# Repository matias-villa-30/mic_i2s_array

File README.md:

# mic_array: 3-microphone sound direction finder (Raspberry Pi Pico 2)

Three I2S MEMS microphones sampled in lockstep by a Raspberry Pi Pico 2, bare metal, no RTOS. The firmware measures **how many samples later each microphone hears a sound** (TDOA, time difference of arrival) and turns those delays into an **azimuth angle** toward the source.

> **Purpose of the project:** a sound-direction sensor for a **UGV (unmanned ground vehicle)**, so the robot can tell which way a sound came from.
> **The servo in this repository is only a test rig.** It is a quick, visible way to check that the angle is right (a pointer that swings toward a clap). It is not part of the final design. In the UGV the azimuth value would go to the drive/navigation code instead.

Author: Matias Villa

---

## Contents

- [How it works](#how-it-works)
- [Repository layout](#repository-layout)
- [Hardware](#hardware)
- [The PCB](#the-pcb)
- [Pin mapping](#pin-mapping)
- [Build and flash](#build-and-flash)
  - [Linux (with the helper scripts)](#linux-with-the-helper-scripts)
  - [Windows](#windows)
  - [macOS](#macos)
- [Testing](#testing)
- [Tuning](#tuning)
- [Status and known limits](#status-and-known-limits)

---

## How it works

```
3 mics --I2S--> PIO --> RX FIFO --DMA--> ring buffer (RAM) --> main loop
```

- **One clock for all mics.** A PIO program generates BCLK (GPIO20) and WS (GPIO21) and samples **four consecutive GPIOs on every BCLK tick**. Each mic has its own data wire, so each 4-bit group contains one bit per mic. All three mics are therefore sampled at the same instant, which is what makes sub-millisecond delay measurement possible.
- **DMA ring buffer.** DMA copies every word into a 32 KB ring without stopping, so the mic clock never stalls while the CPU is busy.
- **Sample rate** is about 48 kHz (150 MHz / 24.4 / 2 / 64), 24-bit samples. One sample is 20.8 µs, which is about 7.15 mm of sound travel.

The main loop works on a window of the newest 512 frames (10.7 ms):

1. **Snapshot**: copy and decode the newest 512 frames out of the ring.
2. **Gate**: if any mic's peak-to-peak level is below `TDOA_GATE`, skip the window (a quiet room would only correlate noise).
3. **Center**: subtract each mic's mean to remove the DC offset (about -360000 counts).
4. **Correlate**: for each pair (1-2, 1-3, 2-3) try every shift from `-MAX_SHIFT` to `+MAX_SHIFT` and keep the one with the best cross-correlation score.
5. **Confidence**: the score is divided by `sqrt(energy_a * energy_b)`, giving -1..+1 per pair. Below `MIN_CONF` the mics did not hear the same sound, so the window is ignored.
6. **Direction**: the three delays are combined by least squares (far-field plane-wave model) into a direction vector, then an azimuth. A consistency check (`k13` should equal `k12 + k23`) rejects windows where one pair locked onto the wrong peak. The last few angles are median-filtered.
7. **Servo (test rig)**: the servo steps toward the angle, at most 15° per update.

### Delay convention

`k > 0` means the **second** mic of the pair hears the sound `k` samples **later**.
`check = k13 - (k12 + k23)` must be about 0, because delay(1→3) = delay(1→2) + delay(2→3).

### Sample format

Each mic's raw 32-bit word has the I2S delay bit on top, so it is decoded as `((int32_t)(w << 1)) >> 8`: a signed 24-bit value (full scale ±8388608).

---

## Repository layout

```
mic_array/
├── CMakeLists.txt      Pico SDK build file
├── mic_i2s.pio         PIO program: BCLK/WS generation + 4-pin parallel sampling
├── src/
│   ├── main.c          setup, DMA ring, main loop
│   ├── mic_tdoa.c      cross-correlation, best-shift search, mean/energy helpers
│   ├── parse.c         de-interleaving of the PIO words, peak-to-peak level
│   └── servo.c         servo driver + delays-to-azimuth (test rig)
├── include/
│   ├── mic_tdoa.h
│   ├── parse.h         pin/ring/frame constants, TDOA_GATE, MIN_CONF
│   └── servo.h         servo pins/limits and the microphone geometry
├── electrical/         KiCad project (schematic + PCB)
│   ├── mic_array.kicad_pro
│   ├── mic_array.kicad_sch
│   └── mic_array.kicad_pcb
├── docs/
│   └── images/         schematic, PCB and photo images used in this README
├── make.sh             helper: build
├── flash.sh            helper: flash with picotool
└── build/              generated by CMake (not committed)
```

---

## Hardware

| Part | Qty | Notes |
|---|---|---|
| Raspberry Pi Pico 2 | 1 | RP2350, runs at 150 MHz |
| I2S MEMS microphone breakout | 3 | 6-pin breakouts (see the header pinout below) |
| 1x06 female pin socket, 2.54 mm | 3 | one per microphone |
| 100 nF capacitor, 0805 | 3 | decoupling, C1 to C3 |
| 1x20 female pin socket, 2.54 mm | 2 | so the Pico is not soldered to the board |
| Micro servo (optional) | 1 | **test rig only**, signal on GPIO16 |

---

## The PCB

The board lives in [`electrical/`](electrical) (KiCad). It is deliberately simple, and it was made for two reasons:

1. **Learning.** Even a small board is a complete exercise: schematic, footprints, placement, routing, DRC, and getting it manufactured.
2. **Reuse the parts as they are.** The microphones are ready-made breakout boards, already soldered to their pins, and the breakouts carry their own resistors and supporting parts. So the carrier PCB only needs **three 100 nF decoupling capacitors and pin sockets**: the mics plug into sockets and the Pico 2 plugs into sockets. Nothing is soldered that you might want to swap or reuse later.

Board facts:

- Three 1x06 mic sockets (`MIC_1`, `MIC_2`, `MIC_3`), three 100 nF 0805 capacitors (`C1` to `C3`) between 3V3 and GND, one Pico 2 on sockets.
- The mic positions are fixed by the board, because it is a microphone array. This is what defines the baselines used by the direction solver (see [Tuning](#tuning)).
- Board size is about 107.5 x 68.5 mm (Edge.Cuts rectangle).
- Fully routed, DRC clean.
- The mic breakouts plug into the headers horizontally.

### Pictures

**Schematic**

*Full schematic: `MIC_1` to `MIC_3` sockets, `C1` to `C3` (100 nF) on the 3V3 rail, and the Pico 2 pins they connect to.*

**PCB layout**

*Routed board (2D view): the mic sockets in their fixed array positions, the Pico 2 sockets and the traces between them.*

**3D render**

*3D view of the board, useful for checking how the headers and the Pico sit relative to each other.*

### Mic header pinout (all three headers identical)

| Header pin | Signal | Goes to |
|---|---|---|
| 1 | 3V3 | Pico 3V3 (pin 36) |
| 2 | GND | GND |
| 3 | BCLK | shared, Pico GPIO20 |
| 4 | DOUT | **individual**, one Pico GPIO per mic |
| 5 | WS (LRCLK) | shared, Pico GPIO21 |
| 6 | SEL | GND, so every mic talks in the **left** slot only |

Check the silkscreen of your breakouts against this order before plugging them in. The schematic labels the WS net "Data"; it is the word-select line.

---

## Pin mapping

| Signal | Pico 2 physical pin | GPIO |
|---|---|---|
| BCLK (shared) | 26 | GPIO20 |
| WS (shared) | 27 | GPIO21 |
| Mic 1 DOUT | 9 | GPIO6 |
| Mic 2 DOUT | 10 | GPIO7 |
| Mic 3 DOUT | 11 | GPIO8 |
| 3V3 | 36 | |
| GND | 8 | |
| Servo signal (test rig, not on the PCB) | 21 | GPIO16 |

> **Check before flashing:** the data pins in the firmware must match how the mics are wired. The PIO samples a window of 4 consecutive GPIOs starting at `DATA_BASE`, and `mic_pin[]` in `src/parse.c` lists which GPIO belongs to which mic.
> - **This PCB:** `DATA_BASE = 6` and `mic_pin = { 6, 7, 8 }` (window GPIO6..9, GPIO9 unused).
> - **Original breadboard wiring:** `DATA_BASE = 7` and `mic_pin = { 9, 8, 7 }`.
>
> BCLK must stay on the pin directly below WS (WS = BCLK + 1), which it does here.

---

## Build and flash

Everything uses the [Raspberry Pi Pico SDK](https://github.com/raspberrypi/pico-sdk). The CMake project is called `sound` and builds for `pico2`; the output is `build/sound.uf2`. USB serial output is on, UART output is off.

### Linux (with the helper scripts)

**1. Install the tools**

| Distro | Command |
|---|---|
| Arch | `sudo pacman -S cmake arm-none-eabi-gcc arm-none-eabi-newlib picotool` |
| Debian/Ubuntu | `sudo apt install cmake gcc-arm-none-eabi libnewlib-arm-none-eabi build-essential picotool` |

Get the SDK and point `PICO_SDK_PATH` at it:

```bash
git clone https://github.com/raspberrypi/pico-sdk.git ~/pico-sdk
cd ~/pico-sdk && git submodule update --init
echo 'export PICO_SDK_PATH=$HOME/pico-sdk' >> ~/.bashrc   # then open a new shell
```

If your distro does not package `picotool`, build it from <https://github.com/raspberrypi/picotool>.

**2. Configure once**

```bash
mkdir -p build
cd build && cmake .. && cd ..
```

**3. Build with `make.sh`**

```bash
./make.sh
```

The script changes into `build/`, runs `make -j`, and returns. It expects `build/` to exist and to have been configured (step 2). After you move or rename source files, delete `build/` and redo step 2.

**4. Flash with `flash.sh`**

```bash
./flash.sh
```

This runs `picotool load -f build/sound.uf2`. The `-f` flag asks a board that is already running this firmware to reboot into the bootloader by itself. The very first time (or if that fails), put the board in BOOTSEL mode by hand: hold the BOOTSEL button while plugging in USB, then run the script again. You can also drag `build/sound.uf2` onto the `RP2350` drive that appears.

If `picotool` complains about permissions, install the picotool udev rules or run it with `sudo`.

**5. Read the output**

The Pico shows up as a USB serial device, usually `/dev/ttyACM0`.

```bash
screen /dev/ttyACM0 115200        # quit: Ctrl-A, then K
# or
minicom -D /dev/ttyACM0
```

You must be in the right group to open it: `dialout` on Debian/Ubuntu, `uucp` on Arch (`sudo usermod -aG uucp $USER`, then log out and in). Baud rate is ignored by USB CDC, any value works.

### Windows

**Option A: VS Code (easiest).** Install the **Raspberry Pi Pico** extension. It downloads the SDK, the ARM toolchain, CMake, Ninja and picotool for you. Use *Import Project* on this folder, choose board `pico2`, then *Compile* and *Run* (or copy `build/sound.uf2` yourself).

**Option B: command line.**

1. Install the [Arm GNU Toolchain](https://developer.arm.com/downloads/-/arm-gnu-toolchain-downloads) (`arm-none-eabi`), [CMake](https://cmake.org/download/), [Ninja](https://github.com/ninja-build/ninja/releases) and [Git](https://git-scm.com/).
2. Clone the Pico SDK with its submodules and set `PICO_SDK_PATH`:
   ```powershell
   git clone https://github.com/raspberrypi/pico-sdk.git C:\pico-sdk
   cd C:\pico-sdk; git submodule update --init
   setx PICO_SDK_PATH C:\pico-sdk
   ```
   Open a new terminal afterwards.
3. Build:
   ```powershell
   mkdir build
   cd build
   cmake -G Ninja ..
   ninja
   ```
4. Flash: hold **BOOTSEL** while plugging in the Pico, then copy `build\sound.uf2` onto the `RP2350` drive. Or use [picotool for Windows](https://github.com/raspberrypi/pico-sdk-tools/releases): `picotool load -f build\sound.uf2`.
5. Read the output: find the COM port in Device Manager (*Ports*), then open it in PuTTY, Tera Term, or the VS Code serial monitor.

**The helper scripts on Windows:** `make.sh` and `flash.sh` are bash scripts. They run from **Git Bash** as they are, as long as `make` is installed (the Ninja route above does not produce a Makefile, so use the commands in step 3 instead). Under **WSL** building works exactly like Linux, but WSL cannot see the USB board by default, so flash from Windows (step 4) or attach the device with [`usbipd-win`](https://github.com/dorssel/usbipd-win).

### macOS

```bash
brew install cmake picotool
brew install --cask gcc-arm-embedded
git clone https://github.com/raspberrypi/pico-sdk.git ~/pico-sdk
cd ~/pico-sdk && git submodule update --init
export PICO_SDK_PATH=~/pico-sdk
```

Then follow the Linux steps (the scripts work as they are). The serial device is `/dev/tty.usbmodem*`: `screen /dev/tty.usbmodem* 115200`.

---

## Testing

You need a quiet room and a sound that is loud and sharp enough: a **hand clap**, a **finger snap**, or a **1 kHz tone** from a phone.

**1. Power-up check.** Open the serial monitor and reset the board. You should see `|BOOT|`. While the room is quiet the firmware stays silent (windows below `TDOA_GATE` are skipped without printing).

**2. Make a sound.** Each accepted window prints one line:

```
k12=  5 (  104.2 us) | k13=-12 ( -250.0 us) | k23=-16 ( -333.3 us) | check=-1
  -> azimuth 34 deg
```

| Field | Meaning |
|---|---|
| `k12`, `k13`, `k23` | delay between that mic pair in samples (and in µs). Positive: the second mic hears it later. |
| `check` | `k13 - (k12 + k23)`. Should be 0 or ±1. Larger means one pair picked a wrong peak. |
| `azimuth` | direction in degrees from the front axis, positive toward +x. Only printed when the reading passed all checks. |

**3. Sanity tests, in this order:**

1. **Broadside test.** Clap straight in front of the board, equally far from all mics. The delays should be small.
2. **Left/right test.** Clap close to one mic. The pairs involving that mic should show it hearing the sound **first**; walk to the other side and the signs should flip. If the servo moves the wrong way, set `SERVO_REVERSE` to `1` in `servo.h`.
3. **Consistency.** Over several claps `check` should stay at 0 or ±1. If it is regularly larger, raise the loudness (closer or louder source) or check the wiring.
4. **Range.** The maximum possible delay is about `MIC_DISTANCE / speed of sound * 48000` samples, so delays near ±`MAX_SHIFT` mean the correlation hit its search limit and the reading is rejected.

**Servo test rig.** With the servo on GPIO16 (and its own power, common ground) the pointer should swing toward the clap, moving at most 15° per update. `calib_servo()` in `servo.c` does a slow sweep (90 → 0 → 180 → 90) to find the mechanical limits; narrow `SERVO_MIN_US`/`SERVO_MAX_US` in `servo.h` if the servo buzzes at an end. Servos draw current spikes, so power them from a supply that can handle it and not from the Pico's 3V3.

**If nothing is ever printed:** the gate is probably too high for your room or mic gain. Lower `TDOA_GATE` in `parse.h`. A quiet room should be about 10000 to 20000 counts peak-to-peak, and a 1 kHz tone about 35000 or more.

---

## Tuning

| Setting | File | Meaning |
|---|---|---|
| `TDOA_GATE` | `include/parse.h` | loudness threshold (peak-to-peak counts) for running the correlation |
| `MIN_CONF` | `include/parse.h` | minimum match quality per pair, -1..+1 (start at 0.5) |
| `SAMPLES` | `include/mic_tdoa.h` | window length in frames, 512 maximum with the 32 KB ring |
| `MIC_DISTANCE` | `include/mic_tdoa.h` | largest mic spacing in cm; sets `MAX_SHIFT` (25 at 17 cm) |
| `MIC_D12_CM`, `MIC_D13_CM`, `MIC_D23_CM` | `include/servo.h` | measured distances between mic pairs (centre of sound hole to centre of sound hole) |
| `MIC3_SIDE`, `SERVO_FRONT_OFFSET_DEG` | `include/servo.h` | which side mic 3 is on, and where "front" points |
| `DOA_NORM_MIN/MAX`, `DOA_MEDIAN_N` | `include/servo.h` | direction-vector quality limits and angle smoothing length |

The three `MIC_Dxx_CM` values must match the real board. Measure them on your PCB, they define the geometry of the direction solver.

---

## Status and known limits

- **Works:** synchronized 3-mic capture, TDOA between all pairs, confidence rejection, delay-to-azimuth, servo test rig.
- **In progress:** sub-sample (fractional) delay estimation, which needs the delays and the servo interface to move from `int` to `float`.
- **Resolution** is one sample (20.8 µs, about 7.15 mm of sound path) until the sub-sample step is finished.
- **2D only.** Three mics in one plane give azimuth, not elevation. The direction solver assumes a far-field source (a flat wave).
- **Servo range** is ±90° around the front, sounds behind the array are ignored by the test rig.
- **DMA runs about 3 hours** and then stops, because the transfer count is `0xFFFFFFFF` words (384000 words/s). Restart the board, or switch to an endless transfer mode for long runs.
- **Reverberant rooms and speech** produce wrong peaks more easily than claps and tones, which is what the confidence and consistency checks are for.

## License

Released under the [MIT License](LICENSE). This covers the firmware, the helper scripts and the KiCad files in `electrical/`: use, modify and build on it freely, just keep the copyright notice.

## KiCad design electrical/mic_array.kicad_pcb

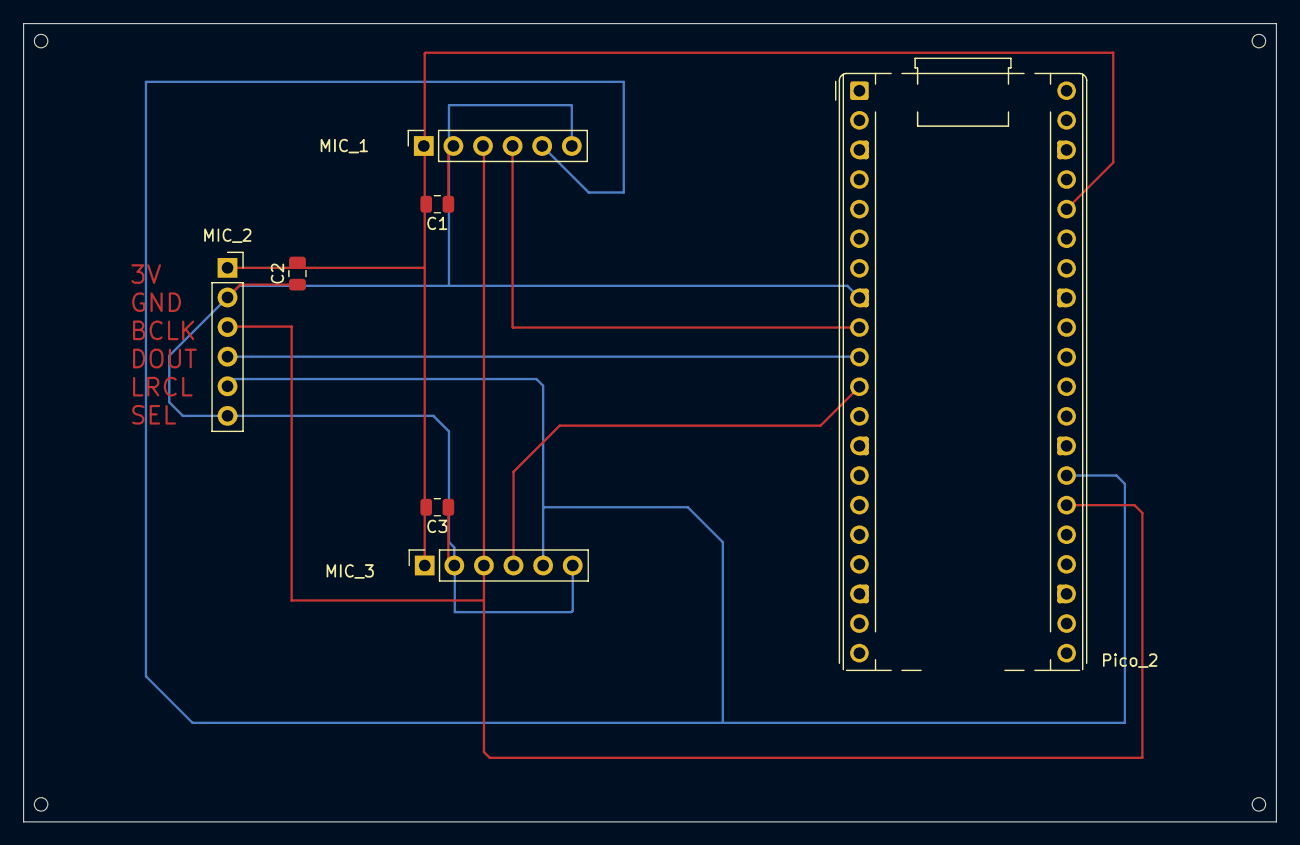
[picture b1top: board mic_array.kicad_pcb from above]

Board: 2 copper layers, 107.5 x 68.5 mm, 7 parts (0 on the bottom side), 7 nets.

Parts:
C1, C2, C3: 100nF; C_0805_2012Metric
MIC_1, MIC_2, MIC_3: Conn_01x06_Socket; PinSocket_1x06_P2.54mm_Vertical
Pico_2: Raspberry Pi Pico 2; RaspberryPi_Pico_Common_THT

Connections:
+3.3V: C1.2, C2.2, C3.2, MIC_1.1, MIC_2.1, MIC_3.1, Pico_2.36
/Clock: MIC_1.3, MIC_2.3, MIC_3.3, Pico_2.26
/Data: MIC_1.5, MIC_2.5, MIC_3.5, Pico_2.27
GND: C1.1, C2.1, C3.1, MIC_1.2, MIC_1.6, MIC_2.2, MIC_2.6, MIC_3.2, MIC_3.6, Pico_2.8
unnamed: MIC_1.4, Pico_2.9
unnamed: MIC_2.4, Pico_2.10
unnamed: MIC_3.4, Pico_2.11
